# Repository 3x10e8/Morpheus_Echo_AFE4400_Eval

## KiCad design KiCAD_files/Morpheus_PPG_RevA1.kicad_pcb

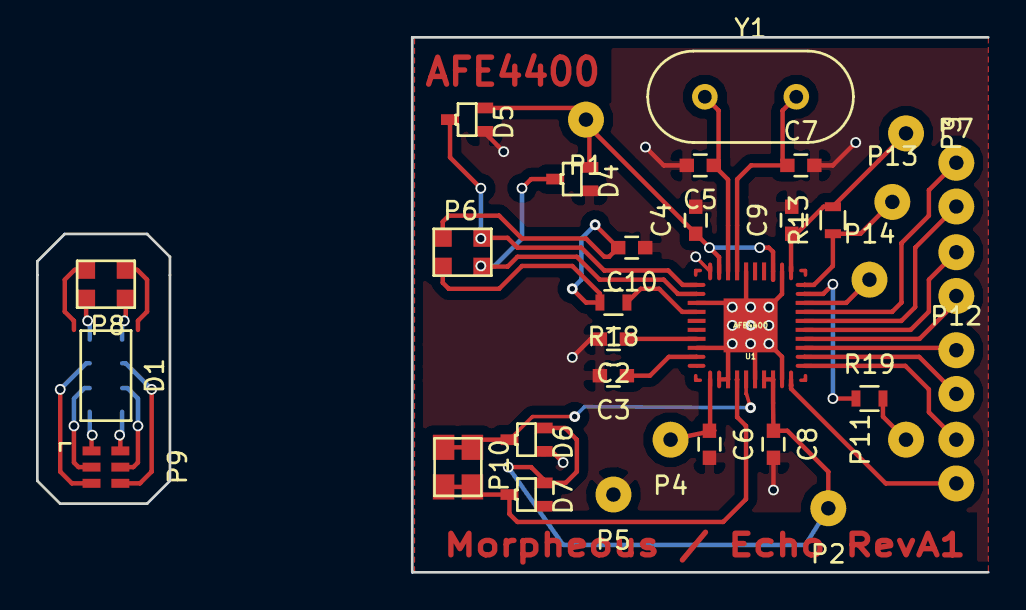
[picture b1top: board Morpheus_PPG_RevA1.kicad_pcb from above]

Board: 2 copper layers, 52.8 x 29.7 mm, 33 parts (0 on the bottom side), 35 nets.

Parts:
C2, C3: 2.2u; C_0603
C4, C6, C9: 0.1u; C_0603
C5, C7: 18p; C_0603
C8: 1u; C_0603
C10: 0.01u; C_0603
D1: SFH_7050; SHF_7050_8pin
D4, D5, D6, D7: D; SOT-323
P1, P2, P3, P4, P5, P11, P13, P14: CONN_01X01; SolderWirePad_single_0-8mmDrill
P6, P8, P10: CONN_01X04; crystal_FA238-TSX3225
P7, P12: CONN_01X04; SolderWirePad_4xLine_0-8mmDrill
P9: CONN_01X06; 6_PADS_LED
R13: 10k; R_0603
R18: 1k; R_0603
R19: 10; R_0603
U1: AFE4400; QFN40-6x6-PN532mirrorRot-0p23mm
Y1: 8M; HC-49V

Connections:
/ADC_RDY: P14.1, U1.28
/AFE_PDN_N: P12.4, U1.20
/CLK_OUT: P13.1, R13.1, U1.30
/DIAG_END: P12.3, U1.21
/LED_ALM: P12.2, U1.22
/PD_ALM: P12.1, U1.23
/RESET_N: P11.1, R19.2
/SCLK: P7.4, U1.24
/SIMO: P7.2, U1.26
/SOMI: P7.3, U1.25
/STE: P7.1, U1.27
GND: C2.2, C3.2, C4.2, C5.2, C6.2, C7.2, C8.2, C9.2, C10.1, D4.1, D5.1, D6.1, D7.1, P5.1, U1.3, U1.8, U1.12, U1.13, U1.16, U1.19, U1.32, U1.36, U1.40, U1.41
unnamed: C2.1, U1.7
unnamed: C3.1, U1.9
unnamed: C5.1, U1.38, Y1.1
unnamed: C7.1, U1.37, Y1.2
unnamed: C10.2, P6.1, P6.4, R18.2
unnamed: D1.1, P9.1
unnamed: D1.2, P9.2
unnamed: D1.3, P9.3
unnamed: D1.4, P8.2
unnamed: D1.5, P8.3
unnamed: D1.6, P9.4
unnamed: D1.7, P9.5
unnamed: D1.8, P9.6
unnamed: D4.3, P6.2, U1.2
unnamed: D5.3, P6.3, U1.1
unnamed: D6.3, P10.3, P10.4, U1.15
unnamed: D7.3, P10.1, P10.2, U1.14
unnamed: R18.1, U1.4
unnamed: R19.1, U1.29
VAA: C4.1, D4.2, D5.2, P1.1, U1.33, U1.39
VCC: C8.1, D6.2, D7.2, P2.1, U1.17, U1.18
VDD: C9.1, P3.1, R13.2, U1.31
VEE: C6.1, P4.1, U1.11

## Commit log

2015-11-17 :octocat: Added .gitattributes & .gitignore files
2015-11-17 Files for backup
    Assimilated files from different directories. May not all work together.
2015-11-18 Corrected DNCs, RESET_N, and simplified traces
    Less cluttered now. All 130 ohm resistors connected to DNC pins have
    been removed (TI uses them for internal testing only.) Pins 29 and 30 on
    the AFE4400 pads appeared reversed, fixed that. Added single connectors
    to utilize space better (compared to multiple pin connectors.)
2015-11-18 Copper traces for silk screen
    Minor corrections (GND) + alignment traces on the corners of AFE4400
